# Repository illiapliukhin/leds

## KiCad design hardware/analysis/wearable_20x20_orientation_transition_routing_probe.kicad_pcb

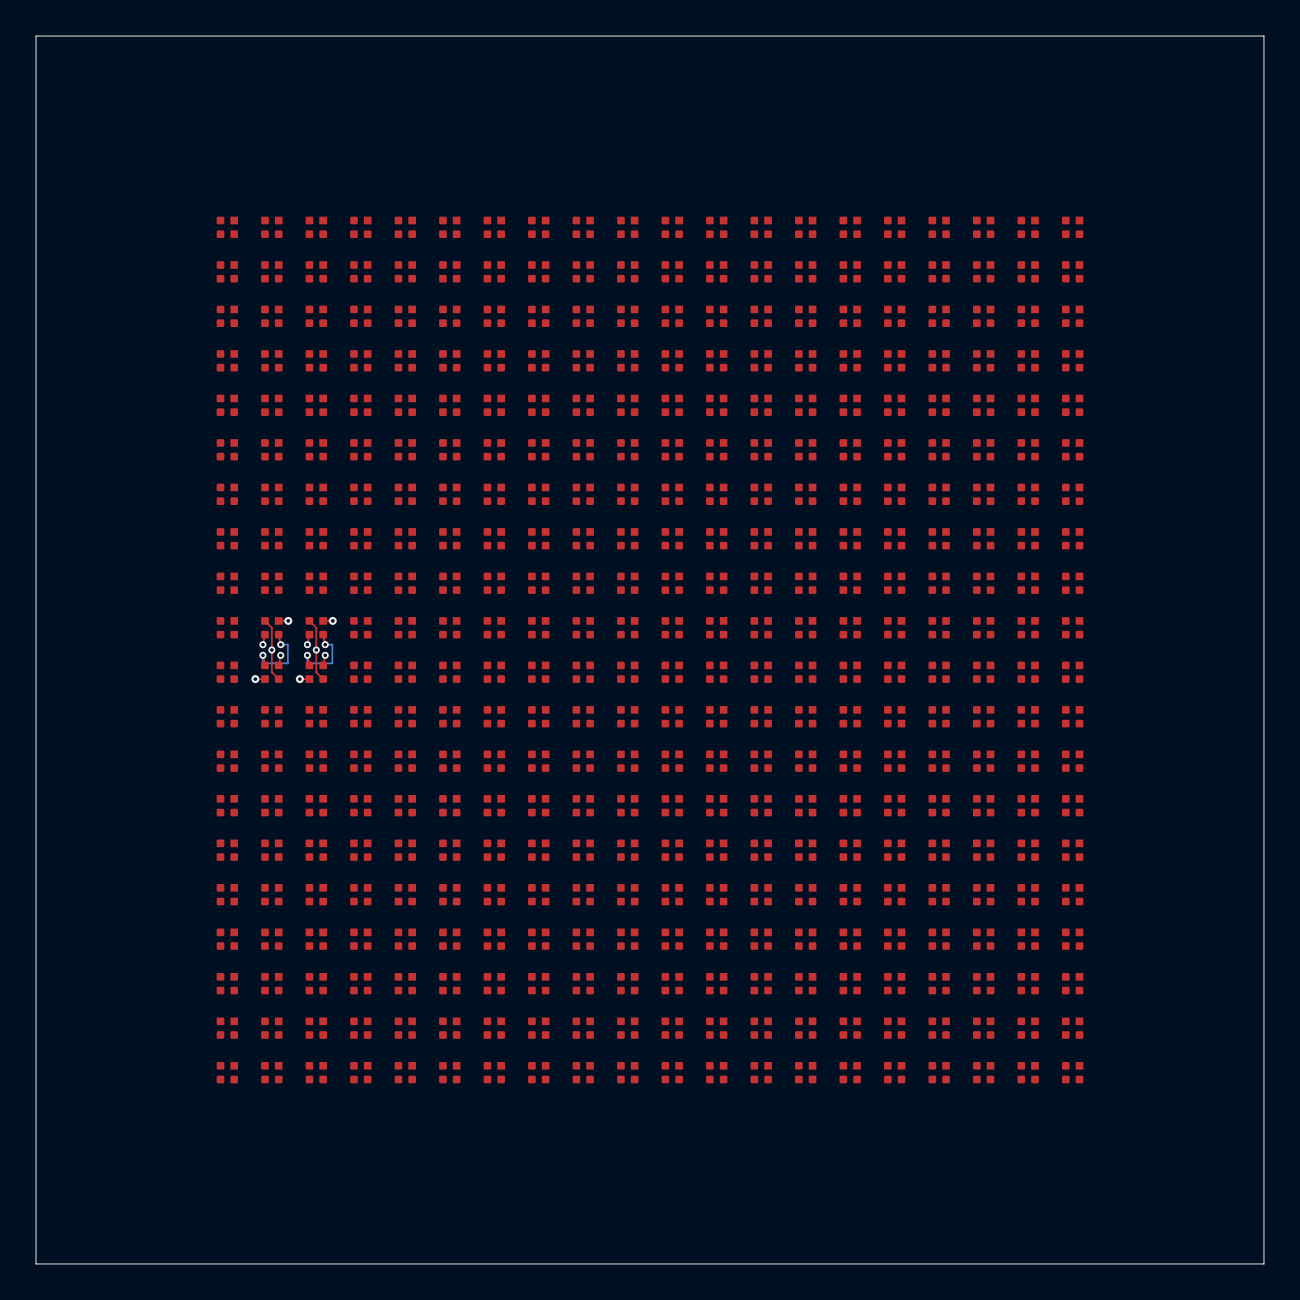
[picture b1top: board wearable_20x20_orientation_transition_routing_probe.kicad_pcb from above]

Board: 4 copper layers, 69.0 x 69.0 mm, 400 parts (0 on the bottom side), 80 nets.

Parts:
D1, D2, D3, D4, D5, D6, D7, D8, D9, D10, D11, D12, D13, D14, D15, D16, D17, D18, D19, D20, D21, D22, D23, D24, D25, D26, D27, D28, D29, D30, D31, D32, D33, D34, D35, D36, D37, D38, D39, D40, D41, D42, D43, D44, D45, D46, D47, D48, D49, D50, D51, D52, D53, D54, D55, D56, D57, D58, D59, D60, D61, D62, D63, D64, D65, D66, D67, D68, D69, D70, D71, D72, D73, D74, D75, D76, D77, D78, D79, D80, D81, D82, D83, D84, D85, D86, D87, D88, D89, D90, D91, D92, D93, D94, D95, D96, D97, D98, D99, D100, D101, D102, D103, D104, D105, D106, D107, D108, D109, D110, D111, D112, D113, D114, D115, D116, D117, D118, D119, D120, D121, D122, D123, D124, D125, D126, D127, D128, D129, D130, D131, D132, D133, D134, D135, D136, D137, D138, D139, D140, D141, D142, D143, D144, D145, D146, D147, D148, D149, D150, D151, D152, D153, D154, D155, D156, D157, D158, D159, D160, D161, D162, D163, D164, D165, D166, D167, D168, D169, D170, D171, D172, D173, D174, D175, D176, D177, D178, D179, D180, D181, D182, D183, D184, D185, D186, D187, D188, D189, D190, D191, D192, D193, D194, D195, D196, D197, D198, D199, D200, D201, D202, D203, D204, D205, D206, D207, D208, D209, D210, D211, D212, D213, D214, D215, D216, D217, D218, D219, D220, D221, D222, D223, D224, D225, D226, D227, D228, D229, D230, D231, D232, D233, D234, D235, D236, D237, D238, D239, D240, D241, D242, D243, D244, D245, D246, D247, D248, D249, D250, D251, D252, D253, D254, D255, D256, D257, D258, D259, D260, D261, D262, D263, D264, D265, D266, D267, D268, D269, D270, D271, D272, D273, D274, D275, D276, D277, D278, D279, D280, D281, D282, D283, D284, D285, D286, D287, D288, D289, D290, D291, D292, D293, D294, D295, D296, D297, D298, D299, D300, D301, D302, D303, D304, D305, D306, D307, D308, D309, D310, D311, D312, D313, D314, D315, D316, D317, D318, D319, D320, D321, D322, D323, D324, D325, D326, D327, D328, D329, D330, D331, D332, D333, D334, D335, D336, D337, D338, D339, D340, D341, D342, D343, D344, D345, D346, D347, D348, D349, D350, D351, D352, D353, D354, D355, D356, D357, D358, D359, D360, D361, D362, D363, D364, D365, D366, D367, D368, D369, D370, D371, D372, D373, D374, D375, D376, D377, D378, D379, D380, D381, D382, D383, D384, D385, D386, D387, D388, D389, D390, D391, D392, D393, D394, D395, D396, D397, D398, D399, D400: MHPA1010RGBDT

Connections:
COL_B_01: D1.4 (K_B), D21.4 (K_B), D41.4 (K_B), D61.4 (K_B), D81.4 (K_B), D101.4 (K_B), D121.4 (K_B), D141.4 (K_B), D161.4 (K_B), D181.4 (K_B), D201.4 (K_B), D221.4 (K_B), D241.4 (K_B), D261.4 (K_B), D281.4 (K_B), D301.4 (K_B), D321.4 (K_B), D341.4 (K_B), D361.4 (K_B), D381.4 (K_B)
COL_B_02: D2.4 (K_B), D22.4 (K_B), D42.4 (K_B), D62.4 (K_B), D82.4 (K_B), D102.4 (K_B), D122.4 (K_B), D142.4 (K_B), D162.4 (K_B), D182.4 (K_B), D202.4 (K_B), D222.4 (K_B), D242.4 (K_B), D262.4 (K_B), D282.4 (K_B), D302.4 (K_B), D322.4 (K_B), D342.4 (K_B), D362.4 (K_B), D382.4 (K_B)
COL_B_03: D3.4 (K_B), D23.4 (K_B), D43.4 (K_B), D63.4 (K_B), D83.4 (K_B), D103.4 (K_B), D123.4 (K_B), D143.4 (K_B), D163.4 (K_B), D183.4 (K_B), D203.4 (K_B), D223.4 (K_B), D243.4 (K_B), D263.4 (K_B), D283.4 (K_B), D303.4 (K_B), D323.4 (K_B), D343.4 (K_B), D363.4 (K_B), D383.4 (K_B)
COL_B_04: D4.4 (K_B), D24.4 (K_B), D44.4 (K_B), D64.4 (K_B), D84.4 (K_B), D104.4 (K_B), D124.4 (K_B), D144.4 (K_B), D164.4 (K_B), D184.4 (K_B), D204.4 (K_B), D224.4 (K_B), D244.4 (K_B), D264.4 (K_B), D284.4 (K_B), D304.4 (K_B), D324.4 (K_B), D344.4 (K_B), D364.4 (K_B), D384.4 (K_B)
COL_B_05: D5.4 (K_B), D25.4 (K_B), D45.4 (K_B), D65.4 (K_B), D85.4 (K_B), D105.4 (K_B), D125.4 (K_B), D145.4 (K_B), D165.4 (K_B), D185.4 (K_B), D205.4 (K_B), D225.4 (K_B), D245.4 (K_B), D265.4 (K_B), D285.4 (K_B), D305.4 (K_B), D325.4 (K_B), D345.4 (K_B), D365.4 (K_B), D385.4 (K_B)
COL_B_06: D6.4 (K_B), D26.4 (K_B), D46.4 (K_B), D66.4 (K_B), D86.4 (K_B), D106.4 (K_B), D126.4 (K_B), D146.4 (K_B), D166.4 (K_B), D186.4 (K_B), D206.4 (K_B), D226.4 (K_B), D246.4 (K_B), D266.4 (K_B), D286.4 (K_B), D306.4 (K_B), D326.4 (K_B), D346.4 (K_B), D366.4 (K_B), D386.4 (K_B)
COL_B_07: D7.4 (K_B), D27.4 (K_B), D47.4 (K_B), D67.4 (K_B), D87.4 (K_B), D107.4 (K_B), D127.4 (K_B), D147.4 (K_B), D167.4 (K_B), D187.4 (K_B), D207.4 (K_B), D227.4 (K_B), D247.4 (K_B), D267.4 (K_B), D287.4 (K_B), D307.4 (K_B), D327.4 (K_B), D347.4 (K_B), D367.4 (K_B), D387.4 (K_B)
COL_B_08: D8.4 (K_B), D28.4 (K_B), D48.4 (K_B), D68.4 (K_B), D88.4 (K_B), D108.4 (K_B), D128.4 (K_B), D148.4 (K_B), D168.4 (K_B), D188.4 (K_B), D208.4 (K_B), D228.4 (K_B), D248.4 (K_B), D268.4 (K_B), D288.4 (K_B), D308.4 (K_B), D328.4 (K_B), D348.4 (K_B), D368.4 (K_B), D388.4 (K_B)
COL_B_09: D9.4 (K_B), D29.4 (K_B), D49.4 (K_B), D69.4 (K_B), D89.4 (K_B), D109.4 (K_B), D129.4 (K_B), D149.4 (K_B), D169.4 (K_B), D189.4 (K_B), D209.4 (K_B), D229.4 (K_B), D249.4 (K_B), D269.4 (K_B), D289.4 (K_B), D309.4 (K_B), D329.4 (K_B), D349.4 (K_B), D369.4 (K_B), D389.4 (K_B)
COL_B_10: D10.4 (K_B), D30.4 (K_B), D50.4 (K_B), D70.4 (K_B), D90.4 (K_B), D110.4 (K_B), D130.4 (K_B), D150.4 (K_B), D170.4 (K_B), D190.4 (K_B), D210.4 (K_B), D230.4 (K_B), D250.4 (K_B), D270.4 (K_B), D290.4 (K_B), D310.4 (K_B), D330.4 (K_B), D350.4 (K_B), D370.4 (K_B), D390.4 (K_B)
COL_B_11: D11.4 (K_B), D31.4 (K_B), D51.4 (K_B), D71.4 (K_B), D91.4 (K_B), D111.4 (K_B), D131.4 (K_B), D151.4 (K_B), D171.4 (K_B), D191.4 (K_B), D211.4 (K_B), D231.4 (K_B), D251.4 (K_B), D271.4 (K_B), D291.4 (K_B), D311.4 (K_B), D331.4 (K_B), D351.4 (K_B), D371.4 (K_B), D391.4 (K_B)
COL_B_12: D12.4 (K_B), D32.4 (K_B), D52.4 (K_B), D72.4 (K_B), D92.4 (K_B), D112.4 (K_B), D132.4 (K_B), D152.4 (K_B), D172.4 (K_B), D192.4 (K_B), D212.4 (K_B), D232.4 (K_B), D252.4 (K_B), D272.4 (K_B), D292.4 (K_B), D312.4 (K_B), D332.4 (K_B), D352.4 (K_B), D372.4 (K_B), D392.4 (K_B)
COL_B_13: D13.4 (K_B), D33.4 (K_B), D53.4 (K_B), D73.4 (K_B), D93.4 (K_B), D113.4 (K_B), D133.4 (K_B), D153.4 (K_B), D173.4 (K_B), D193.4 (K_B), D213.4 (K_B), D233.4 (K_B), D253.4 (K_B), D273.4 (K_B), D293.4 (K_B), D313.4 (K_B), D333.4 (K_B), D353.4 (K_B), D373.4 (K_B), D393.4 (K_B)
COL_B_14: D14.4 (K_B), D34.4 (K_B), D54.4 (K_B), D74.4 (K_B), D94.4 (K_B), D114.4 (K_B), D134.4 (K_B), D154.4 (K_B), D174.4 (K_B), D194.4 (K_B), D214.4 (K_B), D234.4 (K_B), D254.4 (K_B), D274.4 (K_B), D294.4 (K_B), D314.4 (K_B), D334.4 (K_B), D354.4 (K_B), D374.4 (K_B), D394.4 (K_B)
COL_B_15: D15.4 (K_B), D35.4 (K_B), D55.4 (K_B), D75.4 (K_B), D95.4 (K_B), D115.4 (K_B), D135.4 (K_B), D155.4 (K_B), D175.4 (K_B), D195.4 (K_B), D215.4 (K_B), D235.4 (K_B), D255.4 (K_B), D275.4 (K_B), D295.4 (K_B), D315.4 (K_B), D335.4 (K_B), D355.4 (K_B), D375.4 (K_B), D395.4 (K_B)
COL_B_16: D16.4 (K_B), D36.4 (K_B), D56.4 (K_B), D76.4 (K_B), D96.4 (K_B), D116.4 (K_B), D136.4 (K_B), D156.4 (K_B), D176.4 (K_B), D196.4 (K_B), D216.4 (K_B), D236.4 (K_B), D256.4 (K_B), D276.4 (K_B), D296.4 (K_B), D316.4 (K_B), D336.4 (K_B), D356.4 (K_B), D376.4 (K_B), D396.4 (K_B)
COL_B_17: D17.4 (K_B), D37.4 (K_B), D57.4 (K_B), D77.4 (K_B), D97.4 (K_B), D117.4 (K_B), D137.4 (K_B), D157.4 (K_B), D177.4 (K_B), D197.4 (K_B), D217.4 (K_B), D237.4 (K_B), D257.4 (K_B), D277.4 (K_B), D297.4 (K_B), D317.4 (K_B), D337.4 (K_B), D357.4 (K_B), D377.4 (K_B), D397.4 (K_B)
COL_B_18: D18.4 (K_B), D38.4 (K_B), D58.4 (K_B), D78.4 (K_B), D98.4 (K_B), D118.4 (K_B), D138.4 (K_B), D158.4 (K_B), D178.4 (K_B), D198.4 (K_B), D218.4 (K_B), D238.4 (K_B), D258.4 (K_B), D278.4 (K_B), D298.4 (K_B), D318.4 (K_B), D338.4 (K_B), D358.4 (K_B), D378.4 (K_B), D398.4 (K_B)
COL_B_19: D19.4 (K_B), D39.4 (K_B), D59.4 (K_B), D79.4 (K_B), D99.4 (K_B), D119.4 (K_B), D139.4 (K_B), D159.4 (K_B), D179.4 (K_B), D199.4 (K_B), D219.4 (K_B), D239.4 (K_B), D259.4 (K_B), D279.4 (K_B), D299.4 (K_B), D319.4 (K_B), D339.4 (K_B), D359.4 (K_B), D379.4 (K_B), D399.4 (K_B)
COL_B_20: D20.4 (K_B), D40.4 (K_B), D60.4 (K_B), D80.4 (K_B), D100.4 (K_B), D120.4 (K_B), D140.4 (K_B), D160.4 (K_B), D180.4 (K_B), D200.4 (K_B), D220.4 (K_B), D240.4 (K_B), D260.4 (K_B), D280.4 (K_B), D300.4 (K_B), D320.4 (K_B), D340.4 (K_B), D360.4 (K_B), D380.4 (K_B), D400.4 (K_B)
COL_G_01: D1.3 (K_G), D21.3 (K_G), D41.3 (K_G), D61.3 (K_G), D81.3 (K_G), D101.3 (K_G), D121.3 (K_G), D141.3 (K_G), D161.3 (K_G), D181.3 (K_G), D201.3 (K_G), D221.3 (K_G), D241.3 (K_G), D261.3 (K_G), D281.3 (K_G), D301.3 (K_G), D321.3 (K_G), D341.3 (K_G), D361.3 (K_G), D381.3 (K_G)
COL_G_02: D2.3 (K_G), D22.3 (K_G), D42.3 (K_G), D62.3 (K_G), D82.3 (K_G), D102.3 (K_G), D122.3 (K_G), D142.3 (K_G), D162.3 (K_G), D182.3 (K_G), D202.3 (K_G), D222.3 (K_G), D242.3 (K_G), D262.3 (K_G), D282.3 (K_G), D302.3 (K_G), D322.3 (K_G), D342.3 (K_G), D362.3 (K_G), D382.3 (K_G)
COL_G_03: D3.3 (K_G), D23.3 (K_G), D43.3 (K_G), D63.3 (K_G), D83.3 (K_G), D103.3 (K_G), D123.3 (K_G), D143.3 (K_G), D163.3 (K_G), D183.3 (K_G), D203.3 (K_G), D223.3 (K_G), D243.3 (K_G), D263.3 (K_G), D283.3 (K_G), D303.3 (K_G), D323.3 (K_G), D343.3 (K_G), D363.3 (K_G), D383.3 (K_G)
COL_G_04: D4.3 (K_G), D24.3 (K_G), D44.3 (K_G), D64.3 (K_G), D84.3 (K_G), D104.3 (K_G), D124.3 (K_G), D144.3 (K_G), D164.3 (K_G), D184.3 (K_G), D204.3 (K_G), D224.3 (K_G), D244.3 (K_G), D264.3 (K_G), D284.3 (K_G), D304.3 (K_G), D324.3 (K_G), D344.3 (K_G), D364.3 (K_G), D384.3 (K_G)
COL_G_05: D5.3 (K_G), D25.3 (K_G), D45.3 (K_G), D65.3 (K_G), D85.3 (K_G), D105.3 (K_G), D125.3 (K_G), D145.3 (K_G), D165.3 (K_G), D185.3 (K_G), D205.3 (K_G), D225.3 (K_G), D245.3 (K_G), D265.3 (K_G), D285.3 (K_G), D305.3 (K_G), D325.3 (K_G), D345.3 (K_G), D365.3 (K_G), D385.3 (K_G)
COL_G_06: D6.3 (K_G), D26.3 (K_G), D46.3 (K_G), D66.3 (K_G), D86.3 (K_G), D106.3 (K_G), D126.3 (K_G), D146.3 (K_G), D166.3 (K_G), D186.3 (K_G), D206.3 (K_G), D226.3 (K_G), D246.3 (K_G), D266.3 (K_G), D286.3 (K_G), D306.3 (K_G), D326.3 (K_G), D346.3 (K_G), D366.3 (K_G), D386.3 (K_G)
COL_G_07: D7.3 (K_G), D27.3 (K_G), D47.3 (K_G), D67.3 (K_G), D87.3 (K_G), D107.3 (K_G), D127.3 (K_G), D147.3 (K_G), D167.3 (K_G), D187.3 (K_G), D207.3 (K_G), D227.3 (K_G), D247.3 (K_G), D267.3 (K_G), D287.3 (K_G), D307.3 (K_G), D327.3 (K_G), D347.3 (K_G), D367.3 (K_G), D387.3 (K_G)
COL_G_08: D8.3 (K_G), D28.3 (K_G), D48.3 (K_G), D68.3 (K_G), D88.3 (K_G), D108.3 (K_G), D128.3 (K_G), D148.3 (K_G), D168.3 (K_G), D188.3 (K_G), D208.3 (K_G), D228.3 (K_G), D248.3 (K_G), D268.3 (K_G), D288.3 (K_G), D308.3 (K_G), D328.3 (K_G), D348.3 (K_G), D368.3 (K_G), D388.3 (K_G)
COL_G_09: D9.3 (K_G), D29.3 (K_G), D49.3 (K_G), D69.3 (K_G), D89.3 (K_G), D109.3 (K_G), D129.3 (K_G), D149.3 (K_G), D169.3 (K_G), D189.3 (K_G), D209.3 (K_G), D229.3 (K_G), D249.3 (K_G), D269.3 (K_G), D289.3 (K_G), D309.3 (K_G), D329.3 (K_G), D349.3 (K_G), D369.3 (K_G), D389.3 (K_G)
COL_G_10: D10.3 (K_G), D30.3 (K_G), D50.3 (K_G), D70.3 (K_G), D90.3 (K_G), D110.3 (K_G), D130.3 (K_G), D150.3 (K_G), D170.3 (K_G), D190.3 (K_G), D210.3 (K_G), D230.3 (K_G), D250.3 (K_G), D270.3 (K_G), D290.3 (K_G), D310.3 (K_G), D330.3 (K_G), D350.3 (K_G), D370.3 (K_G), D390.3 (K_G)
COL_G_11: D11.3 (K_G), D31.3 (K_G), D51.3 (K_G), D71.3 (K_G), D91.3 (K_G), D111.3 (K_G), D131.3 (K_G), D151.3 (K_G), D171.3 (K_G), D191.3 (K_G), D211.3 (K_G), D231.3 (K_G), D251.3 (K_G), D271.3 (K_G), D291.3 (K_G), D311.3 (K_G), D331.3 (K_G), D351.3 (K_G), D371.3 (K_G), D391.3 (K_G)
COL_G_12: D12.3 (K_G), D32.3 (K_G), D52.3 (K_G), D72.3 (K_G), D92.3 (K_G), D112.3 (K_G), D132.3 (K_G), D152.3 (K_G), D172.3 (K_G), D192.3 (K_G), D212.3 (K_G), D232.3 (K_G), D252.3 (K_G), D272.3 (K_G), D292.3 (K_G), D312.3 (K_G), D332.3 (K_G), D352.3 (K_G), D372.3 (K_G), D392.3 (K_G)
COL_G_13: D13.3 (K_G), D33.3 (K_G), D53.3 (K_G), D73.3 (K_G), D93.3 (K_G), D113.3 (K_G), D133.3 (K_G), D153.3 (K_G), D173.3 (K_G), D193.3 (K_G), D213.3 (K_G), D233.3 (K_G), D253.3 (K_G), D273.3 (K_G), D293.3 (K_G), D313.3 (K_G), D333.3 (K_G), D353.3 (K_G), D373.3 (K_G), D393.3 (K_G)
COL_G_14: D14.3 (K_G), D34.3 (K_G), D54.3 (K_G), D74.3 (K_G), D94.3 (K_G), D114.3 (K_G), D134.3 (K_G), D154.3 (K_G), D174.3 (K_G), D194.3 (K_G), D214.3 (K_G), D234.3 (K_G), D254.3 (K_G), D274.3 (K_G), D294.3 (K_G), D314.3 (K_G), D334.3 (K_G), D354.3 (K_G), D374.3 (K_G), D394.3 (K_G)
COL_G_15: D15.3 (K_G), D35.3 (K_G), D55.3 (K_G), D75.3 (K_G), D95.3 (K_G), D115.3 (K_G), D135.3 (K_G), D155.3 (K_G), D175.3 (K_G), D195.3 (K_G), D215.3 (K_G), D235.3 (K_G), D255.3 (K_G), D275.3 (K_G), D295.3 (K_G), D315.3 (K_G), D335.3 (K_G), D355.3 (K_G), D375.3 (K_G), D395.3 (K_G)
COL_G_16: D16.3 (K_G), D36.3 (K_G), D56.3 (K_G), D76.3 (K_G), D96.3 (K_G), D116.3 (K_G), D136.3 (K_G), D156.3 (K_G), D176.3 (K_G), D196.3 (K_G), D216.3 (K_G), D236.3 (K_G), D256.3 (K_G), D276.3 (K_G), D296.3 (K_G), D316.3 (K_G), D336.3 (K_G), D356.3 (K_G), D376.3 (K_G), D396.3 (K_G)
COL_G_17: D17.3 (K_G), D37.3 (K_G), D57.3 (K_G), D77.3 (K_G), D97.3 (K_G), D117.3 (K_G), D137.3 (K_G), D157.3 (K_G), D177.3 (K_G), D197.3 (K_G), D217.3 (K_G), D237.3 (K_G), D257.3 (K_G), D277.3 (K_G), D297.3 (K_G), D317.3 (K_G), D337.3 (K_G), D357.3 (K_G), D377.3 (K_G), D397.3 (K_G)
COL_G_18: D18.3 (K_G), D38.3 (K_G), D58.3 (K_G), D78.3 (K_G), D98.3 (K_G), D118.3 (K_G), D138.3 (K_G), D158.3 (K_G), D178.3 (K_G), D198.3 (K_G), D218.3 (K_G), D238.3 (K_G), D258.3 (K_G), D278.3 (K_G), D298.3 (K_G), D318.3 (K_G), D338.3 (K_G), D358.3 (K_G), D378.3 (K_G), D398.3 (K_G)
COL_G_19: D19.3 (K_G), D39.3 (K_G), D59.3 (K_G), D79.3 (K_G), D99.3 (K_G), D119.3 (K_G), D139.3 (K_G), D159.3 (K_G), D179.3 (K_G), D199.3 (K_G), D219.3 (K_G), D239.3 (K_G), D259.3 (K_G), D279.3 (K_G), D299.3 (K_G), D319.3 (K_G), D339.3 (K_G), D359.3 (K_G), D379.3 (K_G), D399.3 (K_G)
COL_G_20: D20.3 (K_G), D40.3 (K_G), D60.3 (K_G), D80.3 (K_G), D100.3 (K_G), D120.3 (K_G), D140.3 (K_G), D160.3 (K_G), D180.3 (K_G), D200.3 (K_G), D220.3 (K_G), D240.3 (K_G), D260.3 (K_G), D280.3 (K_G), D300.3 (K_G), D320.3 (K_G), D340.3 (K_G), D360.3 (K_G), D380.3 (K_G), D400.3 (K_G)
COL_R_01: D1.2 (K_R), D21.2 (K_R), D41.2 (K_R), D61.2 (K_R), D81.2 (K_R), D101.2 (K_R), D121.2 (K_R), D141.2 (K_R), D161.2 (K_R), D181.2 (K_R), D201.2 (K_R), D221.2 (K_R), D241.2 (K_R), D261.2 (K_R), D281.2 (K_R), D301.2 (K_R), D321.2 (K_R), D341.2 (K_R), D361.2 (K_R), D381.2 (K_R)
COL_R_02: D2.2 (K_R), D22.2 (K_R), D42.2 (K_R), D62.2 (K_R), D82.2 (K_R), D102.2 (K_R), D122.2 (K_R), D142.2 (K_R), D162.2 (K_R), D182.2 (K_R), D202.2 (K_R), D222.2 (K_R), D242.2 (K_R), D262.2 (K_R), D282.2 (K_R), D302.2 (K_R), D322.2 (K_R), D342.2 (K_R), D362.2 (K_R), D382.2 (K_R)
COL_R_03: D3.2 (K_R), D23.2 (K_R), D43.2 (K_R), D63.2 (K_R), D83.2 (K_R), D103.2 (K_R), D123.2 (K_R), D143.2 (K_R), D163.2 (K_R), D183.2 (K_R), D203.2 (K_R), D223.2 (K_R), D243.2 (K_R), D263.2 (K_R), D283.2 (K_R), D303.2 (K_R), D323.2 (K_R), D343.2 (K_R), D363.2 (K_R), D383.2 (K_R)
COL_R_04: D4.2 (K_R), D24.2 (K_R), D44.2 (K_R), D64.2 (K_R), D84.2 (K_R), D104.2 (K_R), D124.2 (K_R), D144.2 (K_R), D164.2 (K_R), D184.2 (K_R), D204.2 (K_R), D224.2 (K_R), D244.2 (K_R), D264.2 (K_R), D284.2 (K_R), D304.2 (K_R), D324.2 (K_R), D344.2 (K_R), D364.2 (K_R), D384.2 (K_R)
COL_R_05: D5.2 (K_R), D25.2 (K_R), D45.2 (K_R), D65.2 (K_R), D85.2 (K_R), D105.2 (K_R), D125.2 (K_R), D145.2 (K_R), D165.2 (K_R), D185.2 (K_R), D205.2 (K_R), D225.2 (K_R), D245.2 (K_R), D265.2 (K_R), D285.2 (K_R), D305.2 (K_R), D325.2 (K_R), D345.2 (K_R), D365.2 (K_R), D385.2 (K_R)
COL_R_06: D6.2 (K_R), D26.2 (K_R), D46.2 (K_R), D66.2 (K_R), D86.2 (K_R), D106.2 (K_R), D126.2 (K_R), D146.2 (K_R), D166.2 (K_R), D186.2 (K_R), D206.2 (K_R), D226.2 (K_R), D246.2 (K_R), D266.2 (K_R), D286.2 (K_R), D306.2 (K_R), D326.2 (K_R), D346.2 (K_R), D366.2 (K_R), D386.2 (K_R)
COL_R_07: D7.2 (K_R), D27.2 (K_R), D47.2 (K_R), D67.2 (K_R), D87.2 (K_R), D107.2 (K_R), D127.2 (K_R), D147.2 (K_R), D167.2 (K_R), D187.2 (K_R), D207.2 (K_R), D227.2 (K_R), D247.2 (K_R), D267.2 (K_R), D287.2 (K_R), D307.2 (K_R), D327.2 (K_R), D347.2 (K_R), D367.2 (K_R), D387.2 (K_R)
COL_R_08: D8.2 (K_R), D28.2 (K_R), D48.2 (K_R), D68.2 (K_R), D88.2 (K_R), D108.2 (K_R), D128.2 (K_R), D148.2 (K_R), D168.2 (K_R), D188.2 (K_R), D208.2 (K_R), D228.2 (K_R), D248.2 (K_R), D268.2 (K_R), D288.2 (K_R), D308.2 (K_R), D328.2 (K_R), D348.2 (K_R), D368.2 (K_R), D388.2 (K_R)
COL_R_09: D9.2 (K_R), D29.2 (K_R), D49.2 (K_R), D69.2 (K_R), D89.2 (K_R), D109.2 (K_R), D129.2 (K_R), D149.2 (K_R), D169.2 (K_R), D189.2 (K_R), D209.2 (K_R), D229.2 (K_R), D249.2 (K_R), D269.2 (K_R), D289.2 (K_R), D309.2 (K_R), D329.2 (K_R), D349.2 (K_R), D369.2 (K_R), D389.2 (K_R)
COL_R_10: D10.2 (K_R), D30.2 (K_R), D50.2 (K_R), D70.2 (K_R), D90.2 (K_R), D110.2 (K_R), D130.2 (K_R), D150.2 (K_R), D170.2 (K_R), D190.2 (K_R), D210.2 (K_R), D230.2 (K_R), D250.2 (K_R), D270.2 (K_R), D290.2 (K_R), D310.2 (K_R), D330.2 (K_R), D350.2 (K_R), D370.2 (K_R), D390.2 (K_R)
COL_R_11: D11.2 (K_R), D31.2 (K_R), D51.2 (K_R), D71.2 (K_R), D91.2 (K_R), D111.2 (K_R), D131.2 (K_R), D151.2 (K_R), D171.2 (K_R), D191.2 (K_R), D211.2 (K_R), D231.2 (K_R), D251.2 (K_R), D271.2 (K_R), D291.2 (K_R), D311.2 (K_R), D331.2 (K_R), D351.2 (K_R), D371.2 (K_R), D391.2 (K_R)
COL_R_12: D12.2 (K_R), D32.2 (K_R), D52.2 (K_R), D72.2 (K_R), D92.2 (K_R), D112.2 (K_R), D132.2 (K_R), D152.2 (K_R), D172.2 (K_R), D192.2 (K_R), D212.2 (K_R), D232.2 (K_R), D252.2 (K_R), D272.2 (K_R), D292.2 (K_R), D312.2 (K_R), D332.2 (K_R), D352.2 (K_R), D372.2 (K_R), D392.2 (K_R)
COL_R_13: D13.2 (K_R), D33.2 (K_R), D53.2 (K_R), D73.2 (K_R), D93.2 (K_R), D113.2 (K_R), D133.2 (K_R), D153.2 (K_R), D173.2 (K_R), D193.2 (K_R), D213.2 (K_R), D233.2 (K_R), D253.2 (K_R), D273.2 (K_R), D293.2 (K_R), D313.2 (K_R), D333.2 (K_R), D353.2 (K_R), D373.2 (K_R), D393.2 (K_R)
COL_R_14: D14.2 (K_R), D34.2 (K_R), D54.2 (K_R), D74.2 (K_R), D94.2 (K_R), D114.2 (K_R), D134.2 (K_R), D154.2 (K_R), D174.2 (K_R), D194.2 (K_R), D214.2 (K_R), D234.2 (K_R), D254.2 (K_R), D274.2 (K_R), D294.2 (K_R), D314.2 (K_R), D334.2 (K_R), D354.2 (K_R), D374.2 (K_R), D394.2 (K_R)
COL_R_15: D15.2 (K_R), D35.2 (K_R), D55.2 (K_R), D75.2 (K_R), D95.2 (K_R), D115.2 (K_R), D135.2 (K_R), D155.2 (K_R), D175.2 (K_R), D195.2 (K_R), D215.2 (K_R), D235.2 (K_R), D255.2 (K_R), D275.2 (K_R), D295.2 (K_R), D315.2 (K_R), D335.2 (K_R), D355.2 (K_R), D375.2 (K_R), D395.2 (K_R)
COL_R_16: D16.2 (K_R), D36.2 (K_R), D56.2 (K_R), D76.2 (K_R), D96.2 (K_R), D116.2 (K_R), D136.2 (K_R), D156.2 (K_R), D176.2 (K_R), D196.2 (K_R), D216.2 (K_R), D236.2 (K_R), D256.2 (K_R), D276.2 (K_R), D296.2 (K_R), D316.2 (K_R), D336.2 (K_R), D356.2 (K_R), D376.2 (K_R), D396.2 (K_R)
COL_R_17: D17.2 (K_R), D37.2 (K_R), D57.2 (K_R), D77.2 (K_R), D97.2 (K_R), D117.2 (K_R), D137.2 (K_R), D157.2 (K_R), D177.2 (K_R), D197.2 (K_R), D217.2 (K_R), D237.2 (K_R), D257.2 (K_R), D277.2 (K_R), D297.2 (K_R), D317.2 (K_R), D337.2 (K_R), D357.2 (K_R), D377.2 (K_R), D397.2 (K_R)
COL_R_18: D18.2 (K_R), D38.2 (K_R), D58.2 (K_R), D78.2 (K_R), D98.2 (K_R), D118.2 (K_R), D138.2 (K_R), D158.2 (K_R), D178.2 (K_R), D198.2 (K_R), D218.2 (K_R), D238.2 (K_R), D258.2 (K_R), D278.2 (K_R), D298.2 (K_R), D318.2 (K_R), D338.2 (K_R), D358.2 (K_R), D378.2 (K_R), D398.2 (K_R)
COL_R_19: D19.2 (K_R), D39.2 (K_R), D59.2 (K_R), D79.2 (K_R), D99.2 (K_R), D119.2 (K_R), D139.2 (K_R), D159.2 (K_R), D179.2 (K_R), D199.2 (K_R), D219.2 (K_R), D239.2 (K_R), D259.2 (K_R), D279.2 (K_R), D299.2 (K_R), D319.2 (K_R), D339.2 (K_R), D359.2 (K_R), D379.2 (K_R), D399.2 (K_R)
COL_R_20: D20.2 (K_R), D40.2 (K_R), D60.2 (K_R), D80.2 (K_R), D100.2 (K_R), D120.2 (K_R), D140.2 (K_R), D160.2 (K_R), D180.2 (K_R), D200.2 (K_R), D220.2 (K_R), D240.2 (K_R), D260.2 (K_R), D280.2 (K_R), D300.2 (K_R), D320.2 (K_R), D340.2 (K_R), D360.2 (K_R), D380.2 (K_R), D400.2 (K_R)
ROW_01_ANODE: D1.1 (A), D2.1 (A), D3.1 (A), D4.1 (A), D5.1 (A), D6.1 (A), D7.1 (A), D8.1 (A), D9.1 (A), D10.1 (A), D11.1 (A), D12.1 (A), D13.1 (A), D14.1 (A), D15.1 (A), D16.1 (A), D17.1 (A), D18.1 (A), D19.1 (A), D20.1 (A)
ROW_02_ANODE: D21.1 (A), D22.1 (A), D23.1 (A), D24.1 (A), D25.1 (A), D26.1 (A), D27.1 (A), D28.1 (A), D29.1 (A), D30.1 (A), D31.1 (A), D32.1 (A), D33.1 (A), D34.1 (A), D35.1 (A), D36.1 (A), D37.1 (A), D38.1 (A), D39.1 (A), D40.1 (A)
ROW_03_ANODE: D41.1 (A), D42.1 (A), D43.1 (A), D44.1 (A), D45.1 (A), D46.1 (A), D47.1 (A), D48.1 (A), D49.1 (A), D50.1 (A), D51.1 (A), D52.1 (A), D53.1 (A), D54.1 (A), D55.1 (A), D56.1 (A), D57.1 (A), D58.1 (A), D59.1 (A), D60.1 (A)
ROW_04_ANODE: D61.1 (A), D62.1 (A), D63.1 (A), D64.1 (A), D65.1 (A), D66.1 (A), D67.1 (A), D68.1 (A), D69.1 (A), D70.1 (A), D71.1 (A), D72.1 (A), D73.1 (A), D74.1 (A), D75.1 (A), D76.1 (A), D77.1 (A), D78.1 (A), D79.1 (A), D80.1 (A)
ROW_05_ANODE: D81.1 (A), D82.1 (A), D83.1 (A), D84.1 (A), D85.1 (A), D86.1 (A), D87.1 (A), D88.1 (A), D89.1 (A), D90.1 (A), D91.1 (A), D92.1 (A), D93.1 (A), D94.1 (A), D95.1 (A), D96.1 (A), D97.1 (A), D98.1 (A), D99.1 (A), D100.1 (A)
ROW_06_ANODE: D101.1 (A), D102.1 (A), D103.1 (A), D104.1 (A), D105.1 (A), D106.1 (A), D107.1 (A), D108.1 (A), D109.1 (A), D110.1 (A), D111.1 (A), D112.1 (A), D113.1 (A), D114.1 (A), D115.1 (A), D116.1 (A), D117.1 (A), D118.1 (A), D119.1 (A), D120.1 (A)
ROW_07_ANODE: D121.1 (A), D122.1 (A), D123.1 (A), D124.1 (A), D125.1 (A), D126.1 (A), D127.1 (A), D128.1 (A), D129.1 (A), D130.1 (A), D131.1 (A), D132.1 (A), D133.1 (A), D134.1 (A), D135.1 (A), D136.1 (A), D137.1 (A), D138.1 (A), D139.1 (A), D140.1 (A)
ROW_08_ANODE: D141.1 (A), D142.1 (A), D143.1 (A), D144.1 (A), D145.1 (A), D146.1 (A), D147.1 (A), D148.1 (A), D149.1 (A), D150.1 (A), D151.1 (A), D152.1 (A), D153.1 (A), D154.1 (A), D155.1 (A), D156.1 (A), D157.1 (A), D158.1 (A), D159.1 (A), D160.1 (A)
ROW_09_ANODE: D161.1 (A), D162.1 (A), D163.1 (A), D164.1 (A), D165.1 (A), D166.1 (A), D167.1 (A), D168.1 (A), D169.1 (A), D170.1 (A), D171.1 (A), D172.1 (A), D173.1 (A), D174.1 (A), D175.1 (A), D176.1 (A), D177.1 (A), D178.1 (A), D179.1 (A), D180.1 (A)
ROW_10_ANODE: D181.1 (A), D182.1 (A), D183.1 (A), D184.1 (A), D185.1 (A), D186.1 (A), D187.1 (A), D188.1 (A), D189.1 (A), D190.1 (A), D191.1 (A), D192.1 (A), D193.1 (A), D194.1 (A), D195.1 (A), D196.1 (A), D197.1 (A), D198.1 (A), D199.1 (A), D200.1 (A)
ROW_11_ANODE: D201.1 (A), D202.1 (A), D203.1 (A), D204.1 (A), D205.1 (A), D206.1 (A), D207.1 (A), D208.1 (A), D209.1 (A), D210.1 (A), D211.1 (A), D212.1 (A), D213.1 (A), D214.1 (A), D215.1 (A), D216.1 (A), D217.1 (A), D218.1 (A), D219.1 (A), D220.1 (A)
ROW_12_ANODE: D221.1 (A), D222.1 (A), D223.1 (A), D224.1 (A), D225.1 (A), D226.1 (A), D227.1 (A), D228.1 (A), D229.1 (A), D230.1 (A), D231.1 (A), D232.1 (A), D233.1 (A), D234.1 (A), D235.1 (A), D236.1 (A), D237.1 (A), D238.1 (A), D239.1 (A), D240.1 (A)
ROW_13_ANODE: D241.1 (A), D242.1 (A), D243.1 (A), D244.1 (A), D245.1 (A), D246.1 (A), D247.1 (A), D248.1 (A), D249.1 (A), D250.1 (A), D251.1 (A), D252.1 (A), D253.1 (A), D254.1 (A), D255.1 (A), D256.1 (A), D257.1 (A), D258.1 (A), D259.1 (A), D260.1 (A)
ROW_14_ANODE: D261.1 (A), D262.1 (A), D263.1 (A), D264.1 (A), D265.1 (A), D266.1 (A), D267.1 (A), D268.1 (A), D269.1 (A), D270.1 (A), D271.1 (A), D272.1 (A), D273.1 (A), D274.1 (A), D275.1 (A), D276.1 (A), D277.1 (A), D278.1 (A), D279.1 (A), D280.1 (A)
ROW_15_ANODE: D281.1 (A), D282.1 (A), D283.1 (A), D284.1 (A), D285.1 (A), D286.1 (A), D287.1 (A), D288.1 (A), D289.1 (A), D290.1 (A), D291.1 (A), D292.1 (A), D293.1 (A), D294.1 (A), D295.1 (A), D296.1 (A), D297.1 (A), D298.1 (A), D299.1 (A), D300.1 (A)
ROW_16_ANODE: D301.1 (A), D302.1 (A), D303.1 (A), D304.1 (A), D305.1 (A), D306.1 (A), D307.1 (A), D308.1 (A), D309.1 (A), D310.1 (A), D311.1 (A), D312.1 (A), D313.1 (A), D314.1 (A), D315.1 (A), D316.1 (A), D317.1 (A), D318.1 (A), D319.1 (A), D320.1 (A)
ROW_17_ANODE: D321.1 (A), D322.1 (A), D323.1 (A), D324.1 (A), D325.1 (A), D326.1 (A), D327.1 (A), D328.1 (A), D329.1 (A), D330.1 (A), D331.1 (A), D332.1 (A), D333.1 (A), D334.1 (A), D335.1 (A), D336.1 (A), D337.1 (A), D338.1 (A), D339.1 (A), D340.1 (A)
ROW_18_ANODE: D341.1 (A), D342.1 (A), D343.1 (A), D344.1 (A), D345.1 (A), D346.1 (A), D347.1 (A), D348.1 (A), D349.1 (A), D350.1 (A), D351.1 (A), D352.1 (A), D353.1 (A), D354.1 (A), D355.1 (A), D356.1 (A), D357.1 (A), D358.1 (A), D359.1 (A), D360.1 (A)
ROW_19_ANODE: D361.1 (A), D362.1 (A), D363.1 (A), D364.1 (A), D365.1 (A), D366.1 (A), D367.1 (A), D368.1 (A), D369.1 (A), D370.1 (A), D371.1 (A), D372.1 (A), D373.1 (A), D374.1 (A), D375.1 (A), D376.1 (A), D377.1 (A), D378.1 (A), D379.1 (A), D380.1 (A)
ROW_20_ANODE: D381.1 (A), D382.1 (A), D383.1 (A), D384.1 (A), D385.1 (A), D386.1 (A), D387.1 (A), D388.1 (A), D389.1 (A), D390.1 (A), D391.1 (A), D392.1 (A), D393.1 (A), D394.1 (A), D395.1 (A), D396.1 (A), D397.1 (A), D398.1 (A), D399.1 (A), D400.1 (A)
